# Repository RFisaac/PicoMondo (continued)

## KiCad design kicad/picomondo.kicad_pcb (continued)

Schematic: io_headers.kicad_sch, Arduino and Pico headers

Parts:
J14: Arduino power; PinSocket_1x08_P2.54mm_Vertical; MPN B-2200S08P-A120; LCSC C124416
J15: Arduino analog; PinSocket_1x06_P2.54mm_Vertical; MPN B-2200S06P-A120; LCSC C124415
J16: Arduino digital 0-7; PinSocket_1x08_P2.54mm_Vertical; MPN B-2200S08P-A120; LCSC C124416
J17: Arduino digital 8-13; PinSocket_1x10_P2.54mm_Vertical; MPN B-2200S10P-B120; LCSC C124423
J18: Pico left (pins 1-20); PinSocket_1x20_P2.54mm_Vertical; MPN B-2200S20P-A120 (1x20 female); LCSC C124410
J19: Pico right (pins 40-21); PinSocket_1x20_P2.54mm_Vertical; MPN B-2200S20P-A120 (1x20 female); LCSC C124410
JP9: AREF to 3V3; SolderJumper-2_P1.3mm_Open_RoundedPad1.0x1.5mm

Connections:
+3V3: J14.2, J14.4, J19.4, J19.5, J19.6, JP9.2 (B); also elsewhere on the board
+5V: J14.5, J14.8, J19.1, J19.2; also elsewhere on the board
/Arduino and Pico headers/AREF: J17.8, JP9.1 (A)
GND: J14.6, J14.7, J17.7, J18.3, J18.8, J18.13, J18.18, J19.3, J19.8, J19.13, J19.18; also elsewhere on the board
GPIO0: J16.2, J18.1; also elsewhere on the board
GPIO1: J16.1, J18.2; also elsewhere on the board
GPIO2: J16.3, J18.4; also elsewhere on the board
GPIO3: J16.4, J18.5; also elsewhere on the board
GPIO4: J16.5, J18.6; also elsewhere on the board
GPIO5: J16.6, J18.7; also elsewhere on the board
GPIO6: J16.7, J18.9; also elsewhere on the board
GPIO7: J16.8, J18.10; also elsewhere on the board
GPIO8: J18.11; also elsewhere on the board
GPIO9: J18.12; also elsewhere on the board
GPIO10: J18.14; also elsewhere on the board
GPIO11: J18.15; also elsewhere on the board
GPIO12: J18.16; also elsewhere on the board
GPIO13: J18.17; also elsewhere on the board
GPIO14: J18.19; also elsewhere on the board
GPIO15: J18.20; also elsewhere on the board
GPIO16: J17.5, J19.20; also elsewhere on the board
GPIO17: J17.3, J19.19; also elsewhere on the board
GPIO18: J17.6, J19.17; also elsewhere on the board
GPIO19: J17.4, J19.16; also elsewhere on the board
GPIO20: J15.5, J17.9, J19.15; also elsewhere on the board
GPIO21: J15.6, J17.10, J19.14; also elsewhere on the board
GPIO22: J19.12; also elsewhere on the board
GPIO26: J19.10; also elsewhere on the board
GPIO27: J19.9; also elsewhere on the board
GPIO28: J19.7; also elsewhere on the board
GPIO32: J17.1; also elsewhere on the board
GPIO33: J17.2; also elsewhere on the board
GPIO40: J15.1; also elsewhere on the board
GPIO41: J15.2; also elsewhere on the board
GPIO42: J15.3; also elsewhere on the board
GPIO43: J15.4; also elsewhere on the board
RUN: J14.3, J19.11; also elsewhere on the board

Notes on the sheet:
Digital 1x10: D8, D9 = GPIO32, 33; D10 SS = GPIO17; D11 MOSI = GPIO19; D12 MISO = GPIO16; D13 SCK = GPIO18; GND; AREF (joined to +3V3 only if the solder jumper is bridged); SDA, SCL.
Power header 1x8: NC, IOREF (3.3 V logic level), RESET (RUN), 3.3 V, 5 V, GND, GND, VIN (+5V).
Digital 1x8: D0 (RX) = GPIO1, D1 (TX) = GPIO0, D2-D7 = GPIO2-7.
Analog header 1x6: A0-A3 = GPIO40-43 (ADC0-3), A4 = SDA (GPIO20), A5 = SCL (GPIO21).
PICO-COMPATIBLE SOCKETS: two 1x20 female headers, 17.78 mm (700 mil) apart, in the Pico pinout. GP0 = TX, GP1 = RX (Pico convention). GP8/GP9 are also the J7/J8 output enables and GP12-15/GP22 the microSD pins: a Pico accessory must not drive them. VBUS / VSYS are the board's +5V.
ARDUINO UNO R3 SHIELD SOCKETS (female). Pin 1 of each header is at the D0 / A0 / NC / D8 end in this numbering; place them on the Uno R3 hole pattern (KiCad footprint Module:Arduino_UNO_R3 has the exact positions).

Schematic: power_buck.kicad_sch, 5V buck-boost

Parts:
C21, C22, C23, C24: 10u 50V; C_1206_3216Metric; LCSC C7432782
C25: 100n 50V; C_0402_1005Metric; MPN CL05B104KB54PNC; LCSC C307331
C26: 100u 50V; CP_Elec_8x10
C27, C28, C33: 100n 25V; C_0402_1005Metric; MPN CL05B104KB54PNC; LCSC C307331
C29, C30, C31, C32, C34, C35: 22u 16V; C_1206_3216Metric; LCSC C2985039
C36: 10u 16V; C_0805_2012Metric; MPN CL21A106KAYNNNE; LCSC C15850
C37: 10n; C_0402_1005Metric; MPN CL05B103KB5NNNC; LCSC C15195
C38: 3.3n; C_0402_1005Metric; MPN CL05B332KB5NNNC; LCSC C26404
C39: 10p; C_0402_1005Metric; not fitted
L2: 4.7u; L_Coilcraft_XAL1010-XXX; MPN XAL1010-472MED; LCSC C19271849
NT1: AGND-GND; NetTie-2_SMD_Pad0.5mm
Q1, Q2: CSD18543Q3A; VSONP-8_L3.1-W3.1-P0.65-LS3.5-BL; MPN CSD18543Q3A; LCSC C840100
R12: 10m 1% 1W; R_2512_6332Metric; MPN GX2512-2W-10mR-1%; LCSC C500718
R13: 49.9k 1%; R_0402_1005Metric; MPN 0402WGF4992TCE; LCSC C25897
R14: 33.2k 1%; R_0402_1005Metric; MPN 0402WGF3322TCE; LCSC C122548
R15: 100k; R_0402_1005Metric; MPN 0402WGF1003TCE; LCSC C25741
R16: 0; R_0402_1005Metric; MPN 0402WGF0000TCE; LCSC C17168
R17: 7.5k; R_0402_1005Metric; MPN 0402WGF7501TCE; LCSC C25918
R18: 220k 1%; R_0402_1005Metric; MPN 0402WGF2203TCE; LCSC C25767
R19: 88.7k 1%; R_0402_1005Metric; MPN 0402WGF8872TCE; LCSC C25922
R20: 10k; R_0402_1005Metric; MPN 0402WGF1002TCE; LCSC C25744
U4: TPS55288; VQFN-HR-26_L4.0-W3.5_TPS55288RPMR; MPN TPS55288RPMR; LCSC C2864583

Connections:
+3V3: R20.1; also elsewhere on the board
+5V: C34.1, C35.1, R12.2, U4.13 (ISN); also elsewhere on the board
/5V buck-boost/BOOT1: C27.1, U4.22 (BOOT1)
/5V buck-boost/BOOT2: C28.1, U4.20 (BOOT2)
/5V buck-boost/CDC: R15.1, U4.16 (CDC)
/5V buck-boost/COMP: C39.1, R17.1, U4.18 (COMP)
/5V buck-boost/DITH: C37.1, U4.7 (DITH/SYNC)
/5V buck-boost/DR1H: Q1.4 (G), U4.2 (DR1H)
/5V buck-boost/DR1L: Q2.4 (G), U4.1 (DR1L)
/5V buck-boost/EN_UVLO: R18.2, R19.1, U4.4 (EN/UVLO)
/5V buck-boost/FSW: R13.1, U4.8 (FSW)
/5V buck-boost/ILIM: R14.1, U4.17 (ILIM)
/5V buck-boost/MODE: R16.1, U4.15 (MODE)
/5V buck-boost/SW1: C27.2, L2.1, Q1.1 (S), Q1.2 (S), Q1.3 (S), Q2.5 (D), Q2.6 (D), Q2.7 (D), Q2.8 (D), Q2.9 (D), U4.23 (SW1)
/5V buck-boost/SW2: C28.2, L2.2, U4.21 (SW2), U4.25 (SW2)
/5V buck-boost/VCC_TPS: C36.1, U4.19 (VCC)
/5V buck-boost/VOUT_PRE: C29.1, C30.1, C31.1, C32.1, C33.1, R12.1, U4.11 (VOUT), U4.12 (ISP), U4.26 (VOUT)
AGND: C36.2, C37.2, C38.2, C39.2, NT1.1, R13.2, R14.2, R15.2, R16.2, R19.2, U4.10 (AGND)
GND: C21.2, C22.2, C23.2, C24.2, C25.2, C26.2, C29.2, C30.2, C31.2, C32.2, C33.2, C34.2, C35.2, NT1.2, Q2.1 (S), Q2.2 (S), Q2.3 (S), U4.9 (PGND), U4.24 (PGND); also elsewhere on the board
GPIO20: U4.6 (SDA); also elsewhere on the board
GPIO21: U4.5 (SCL); also elsewhere on the board
GPIO35: R20.2, U4.14 (FB/INT); also elsewhere on the board
unnamed: C38.1, R17.2
V_INPUT: C21.1, C22.1, C23.1, C24.1, C25.1, C26.1, Q1.5 (D), Q1.6 (D), Q1.7 (D), Q1.8 (D), Q1.9 (D), R18.1, U4.3 (VIN); also elsewhere on the board

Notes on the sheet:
OUTPUT: 4 x 22 uF 16 V ceramic on the converter side of the sense resistor (the loop is compensated for 10 uF minimum effective capacitance), plus 2 x 22 uF after it. ISP/ISN are Kelvin connections to the two ends of R_SNS: route them as a pair, separate from the power copper.
INPUT: 4 x 10 uF 50 V ceramic (about 20 uF effective after DC-bias derating, TI recommends at least 4.7 uF effective), 100 nF close to the VIN pin. Optional 100 uF bulk (DNP) for long supply leads. Place the ceramics right at the buck-side FET drain and PGND (shortest loop).
CONTROL NETWORK (all AGND returns go to the AGND island, which joins GND only at the net tie next to the VCC capacitor, as in TI's layout example).
POWER STAGE: keep V_INPUT -> Q1 -> Q2 -> GND -> input caps loop tiny; SW1/SW2 traces short and wide, top layer, no vias. Inductor: 4.7 uH, saturation current 12 A or more, DCR 12 mohm or less (Coilcraft XAL1010-472 or equivalent). 0.1 uF bootstrap caps right at BOOT/SW pins.

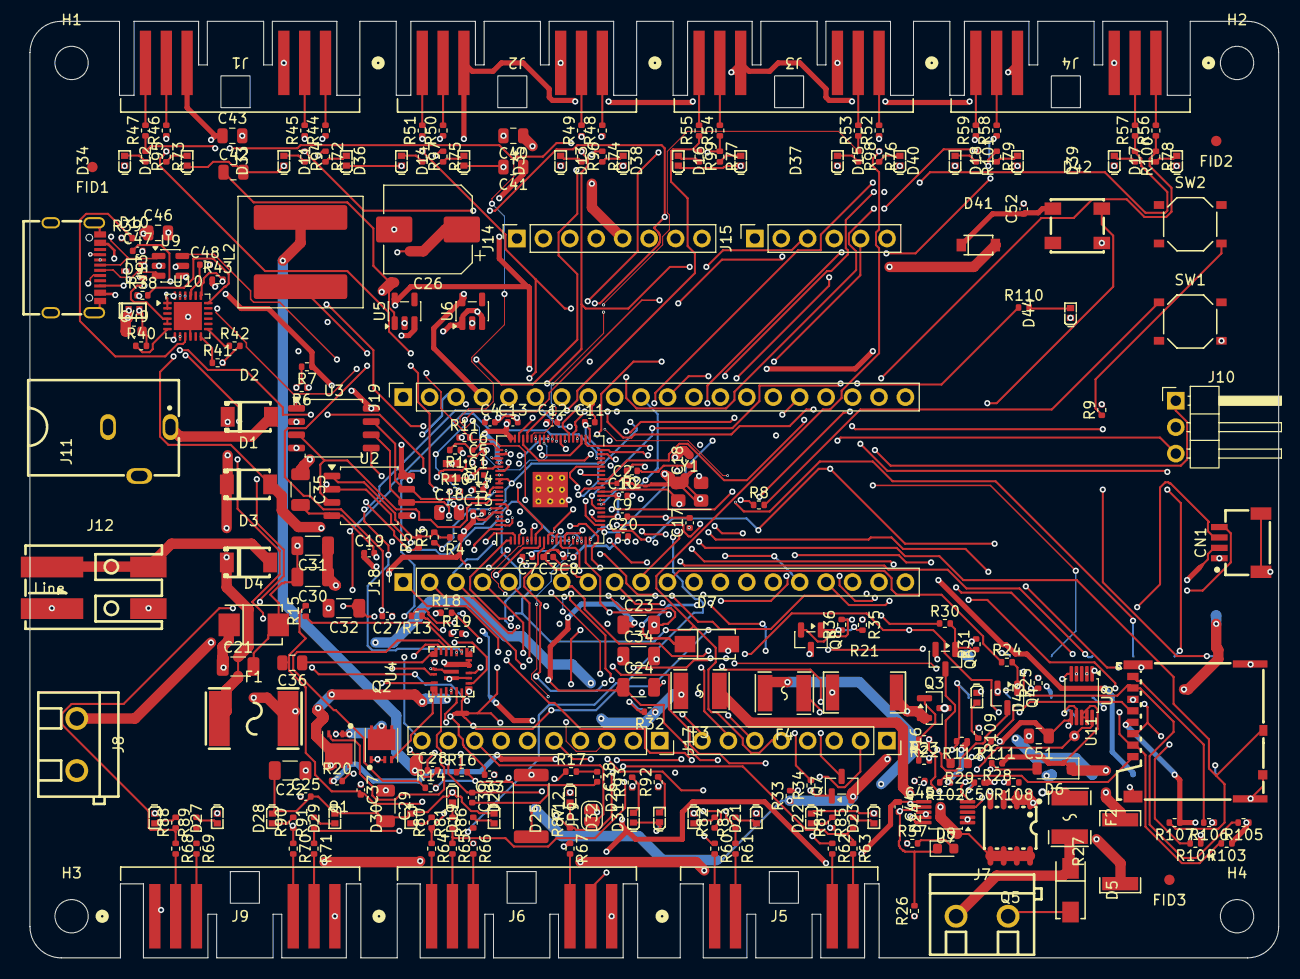
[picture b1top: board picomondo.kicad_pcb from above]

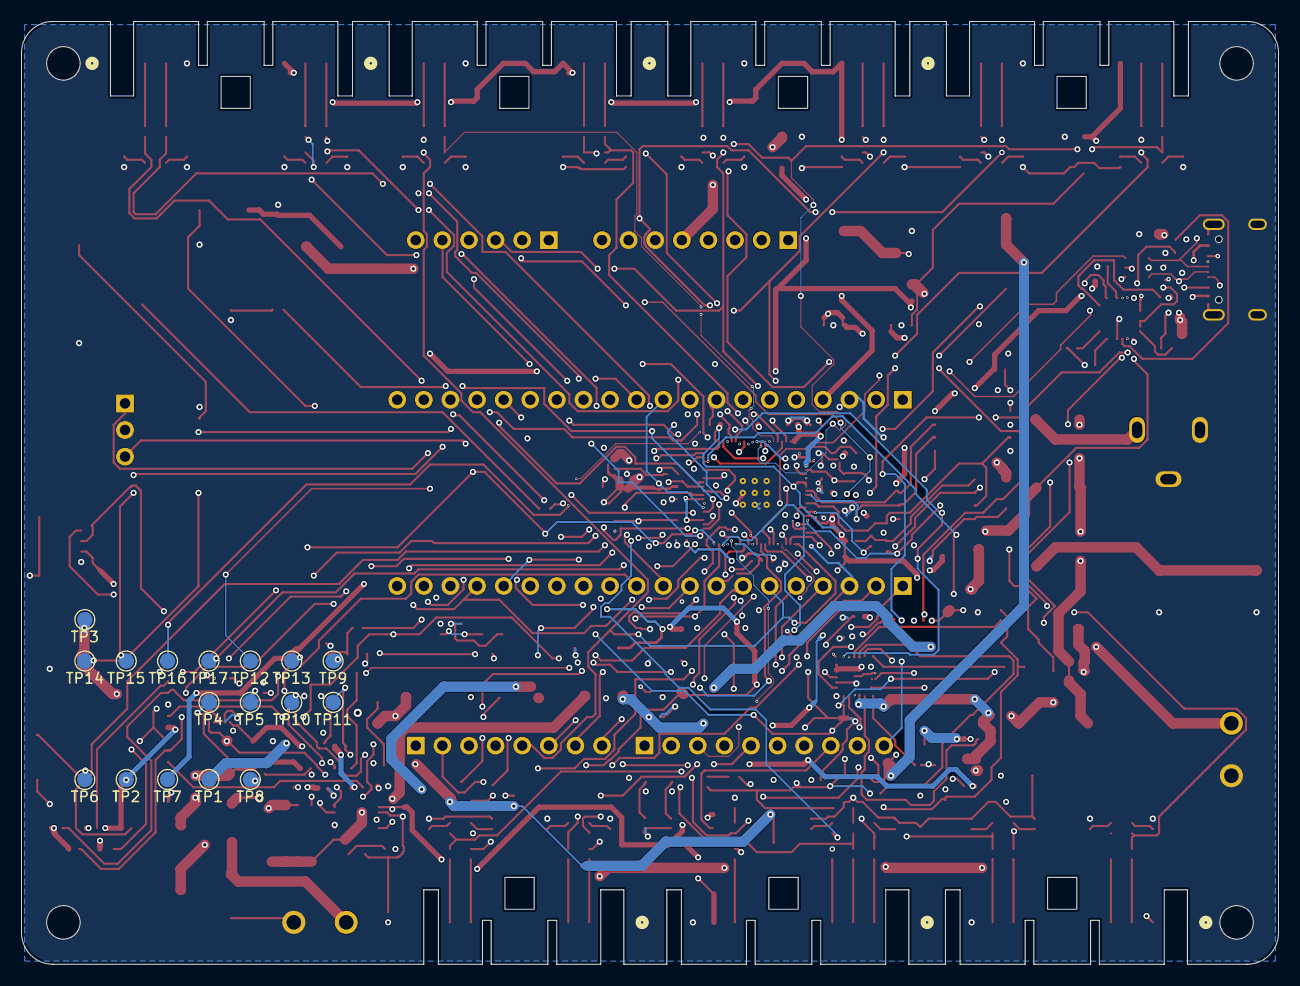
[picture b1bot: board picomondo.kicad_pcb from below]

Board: 4 copper layers, 120.0 x 90.0 mm, 282 parts (17 on the bottom side), 190 nets.

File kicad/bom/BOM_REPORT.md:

# BOM report

Generated by `tools/bom.py` from `picomondo.kicad_pcb`. 240 parts with an LCSC number on 67 line items; 46 extended or preferred line items (JLCPCB charges a loading fee per extended part type; check their current fee schedule). Stock check assumes 5 boards and a 3x margin.

## Line items

| Refs | Qty | Value | LCSC | Type | Stock | Unit price | Note |
|---|---|---|---|---|---|---|---|
| C1,C2,C5... | 4 | 4.7u | C23733 | basic | 2365245 | 0.0167 |  |
| C3,C4,C7... | 20 | 100n | C307331 | basic | 15344796 | 0.0092 |  |
| C17,C18 | 2 | 15p | C106997 | extended | 2278248 | 0.0020 |  |
| C21,C22,C23... | 4 | 10u 50V | C7432782 | extended | 100526 | 0.2051 |  |
| C29,C30,C31... | 6 | 22u 16V | C2985039 | extended | 801 | 0.3191 |  |
| C37 | 1 | 10n | C15195 | basic | 4017940 | 0.0050 |  |
| C38 | 1 | 3.3n | C26404 | preferred | 232147 | 0.0068 |  |
| C16,C36,C40... | 7 | 10u 10V | C15850 | basic | 4904066 | 0.0657 |  |
| C46 | 1 | 4.7u 25V | C1779 | basic | 2968755 | 0.0348 |  |
| C47,C48 | 2 | 1u 10V | C52923 | basic | 8321740 | 0.0108 |  |
| C49 | 1 | 1u 25V | C5673 | extended | 4396637 | 0.0278 |  |
| D1,D2,D3 | 3 | SS54F-HF 5A 40V | C5142774 | extended | 5302 | 0.2241 |  |
| D4 | 1 | SMBJ28A | C178227 | extended | 26078 | 0.1079 |  |
| D6 | 1 | BZT52C12 12V | C177013 | extended | 6524 | 0.0570 |  |
| D5,D7 | 2 | SS54-HF | C22452 | basic | 2389672 | 0.0447 |  |
| D8 | 1 | red | C2286 | basic | 4789156 | 0.0076 |  |
| D9 | 1 | ESDA25P35-1U1M | C1974707 | extended | 1426 | 0.1904 |  |
| D10 | 1 | ESDA25W | C2935152 | extended | 1027 | 0.1444 |  |
| D11,D12,D13... | 32 | white | C7220928 | extended | 545 | 0.2657 |  |
| D41 | 1 | 1N5819HW | C82544 | extended | 138574 | 0.0570 |  |
| D42 | 1 | WS2812B-V5 | C2874885 | extended | 89621 | 0.1107 |  |
| F1 | 1 | 5A hold 30V | C19078763 | extended | 68759 | 0.1610 |  |
| F2,F3,F4 | 3 | 3A hold 33V | C54300298 | extended | 5652 | 0.2187 |  |
| J7,J8 | 2 | J8 V_INPUT out | C474881 | extended | 75284 | 0.1019 |  |
| J10 | 1 | SWD | C239521 | extended | 2288 | 0.2012 |  |
| J11 | 1 | Barrel 5.5x2.1 | C3096093 | extended | 1052 | 1.0956 |  |
| J12 | 1 | Terminal 2P | C2765055 | extended | 27443 |  |  |
| J13 | 1 | USB-C | C3020560 | extended | 591 | 1.3092 |  |
| J14,J16 | 2 | Arduino power | C124416 | extended | 2667 | 0.1777 |  |
| J15 | 1 | Arduino analog | C124415 | extended | 1403 | 0.1246 |  |
| J17 | 1 | Arduino digital 8-13 | C124423 | extended | 4711 | 0.1886 |  |
| J18,J19 | 2 | Pico right (pins 40-21) | C124410 | extended | 1093 | 0.3688 |  |
| L1 | 1 | 3.3u | C42411119 | extended | 1922 | 0.2858 |  |
| L2 | 1 | 4.7u | C19271849 | extended | 157 | 13.3080 |  |
| Q1,Q2 | 2 | CSD18543Q3A | C840100 | extended | 11977 | 0.8017 |  |
| Q4,Q6,Q8 | 3 | MMBT3904 | C81464 | extended | 1556997 | 0.0167 |  |
| Q5 | 1 | DMP4015SSS-13 | C508210 | extended | 2589 | 1.2977 |  |
| Q3,Q7 | 2 | SI2305A | C347488 | extended | 47845 | 0.0409 |  |
| R1 | 1 | 33 | C25105 | basic | 1815062 | 0.0012 |  |
| R10,R11 | 2 | 27 | C25100 | extended | 56281 | 0.0019 |  |
| R12 | 1 | 10m 1% 1W | C500718 | extended | 2320 | 0.0814 |  |
| R13 | 1 | 49.9k 1% | C25897 | preferred | 35168 | 0.0015 |  |
| R14 | 1 | 33.2k 1% | C122548 | extended | 349568 | 0.0007 |  |
| R3,R16 | 2 | 0 | C17168 | basic | 9185166 | 0.0025 |  |
| R17 | 1 | 7.5k | C25918 | preferred | 1196541 | 0.0022 |  |
| R18 | 1 | 220k 1% | C25767 | preferred | 158069 | 0.0023 |  |
| R19 | 1 | 88.7k 1% | C25922 | extended | 101022 | 0.0016 |  |
| R22,R28,R33 | 3 | 47k | C25792 | basic | 5520539 | 0.0026 |  |
| R15,R25,R31... | 6 | 100k | C25741 | basic | 8203089 | 0.0025 |  |
| R21,R27 | 2 | 20m 1% 2W | C500720 | extended | 3543 | 0.0800 |  |
| R29 | 1 | 22k | C31850 | basic | 3694042 | 0.0042 |  |
| R32 | 1 | 22k | C25768 | basic | 813018 | 0.0024 |  |
| R20,R23,R24... | 14 | 10k | C25744 | basic | 21560265 | 0.0034 |  |
| R2,R8,R9... | 5 | 1k | C11702 | basic | 7068307 | 0.0019 |  |
| R43,R111,R112 | 3 | 4.7k | C25900 | basic | 15447153 | 0.0027 |  |
| R44,R45,R46... | 29 | 100 | C25076 | basic | 4079878 | 0.0013 |  |
| R37,R72,R73... | 33 | 470 | C25117 | basic | 844142 | 0.0027 |  |
| SW1,SW2 | 2 | RESET | C318884 | basic | 467503 | 0.0207 |  |
| U1 | 1 | RP2350B | C42415655 | extended | 3393 | 1.2920 |  |
| U2 | 1 | W25Q128JVS | C97521 | basic | 48814 | 2.5782 |  |
| U4 | 1 | TPS55288 | C2864583 | extended | 5147 | 2.2214 |  |
| U5,U6 | 2 | AP2112K-3.3 | C51118 | extended | 37854 | 0.1726 |  |
| U7,U8 | 2 | INA226 (0x40) | C49851 | extended | 43725 | 0.7621 |  |
| U9 | 1 | USBLC6-2SC6 | C7519 | extended | 46944 | 0.1784 |  |
| U10 | 1 | STUSB4500 | C2678061 | extended | 4876 | 2.6826 |  |
| U11 | 1 | microSD | C428492 | extended | 23940 | 1.1476 |  |
| Y1 | 1 | ABM8-272-T3 | C20625731 | extended | 12836 | 0.6255 |  |

## Through-hole parts in the BOM (not in the SMD placement file)

D1, D2, D3, D5, D7, D10, D11, D12, D13, D14, D15, D16, D17, D18, D19, D20, D21, D22, D23, D24, D25, D26, D27, D28, D29, D30, D31, D32, D33, D34, D35, D36, D37, D38, D39, D40, D43, D44, F1, F2, F3, F4, J7, J8, J11, J14, J15, J16, J17, J18, J19

## Footprint-only items (no purchase)

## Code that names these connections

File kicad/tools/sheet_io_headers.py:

"""Arduino Uno R3 shield sockets and Pico-compatible sockets.

Both header sets share the GPIO nets with the EdgeLock connectors; use one accessory class at a
time. On the PCB the Pico sockets sit inside the Arduino pin pattern so the two cannot be
plugged in together.

Arduino UART convention (resolves the old open question): D0 is RX = GPIO1, D1 is TX = GPIO0.
VIN on the Arduino power header is the board's +5V, not the raw input voltage.
"""
FP_SOCKET = "Connector_PinSocket_2.54mm:PinSocket_1x{n:02d}_P2.54mm_Vertical"
CONN = "Connector_Generic:Conn_01x{n:02d}"

ARDUINO = [
    ("Arduino power", 8, {1: None, 2: "+3V3", 3: "RUN", 4: "+3V3", 5: "+5V", 6: "GND", 7: "GND", 8: "+5V"},
     "Power header 1x8: NC, IOREF (3.3 V logic level), RESET (RUN), 3.3 V, 5 V, GND, GND, VIN (+5V)."),
    ("Arduino analog", 6, {1: "GPIO40", 2: "GPIO41", 3: "GPIO42", 4: "GPIO43", 5: "GPIO20", 6: "GPIO21"},
     "Analog header 1x6: A0-A3 = GPIO40-43 (ADC0-3), A4 = SDA (GPIO20), A5 = SCL (GPIO21)."),
    ("Arduino digital 0-7", 8, {1: "GPIO1", 2: "GPIO0", 3: "GPIO2", 4: "GPIO3", 5: "GPIO4", 6: "GPIO5",
                                7: "GPIO6", 8: "GPIO7"},
     "Digital 1x8: D0 (RX) = GPIO1, D1 (TX) = GPIO0, D2-D7 = GPIO2-7."),
    ("Arduino digital 8-13", 10, {1: "GPIO32", 2: "GPIO33", 3: "GPIO17", 4: "GPIO19", 5: "GPIO16",
                                  6: "GPIO18", 7: "GND", 8: "AREF", 9: "GPIO20", 10: "GPIO21"},
     "Digital 1x10: D8, D9 = GPIO32, 33; D10 SS = GPIO17; D11 MOSI = GPIO19; D12 MISO = GPIO16;\n"
     "D13 SCK = GPIO18; GND; AREF (joined to +3V3 only if the solder jumper is bridged); SDA, SCL."),
]

PICO_LEFT = {1: "GPIO0", 2: "GPIO1", 3: "GND", 4: "GPIO2", 5: "GPIO3", 6: "GPIO4", 7: "GPIO5", 8: "GND",
             9: "GPIO6", 10: "GPIO7", 11: "GPIO8", 12: "GPIO9", 13: "GND", 14: "GPIO10", 15: "GPIO11",
             16: "GPIO12", 17: "GPIO13", 18: "GND", 19: "GPIO14", 20: "GPIO15"}
# right row listed from Pico pin 40 down to pin 21
PICO_RIGHT = {1: "+5V", 2: "+5V", 3: "GND", 4: "+3V3", 5: "+3V3", 6: "+3V3", 7: "GPIO28", 8: "GND",
              9: "GPIO27", 10: "GPIO26", 11: "RUN", 12: "GPIO22", 13: "GND", 14: "GPIO21", 15: "GPIO20",
              16: "GPIO19", 17: "GPIO18", 18: "GND", 19: "GPIO17", 20: "GPIO16"}


def socket(s, refs, name, n, pins, x, y, mpn="", extra=None):
    c = s.add(CONN.format(n=n), refs.next("J"), name, FP_SOCKET.format(n=n), x, y,
              extra=dict(extra or {}, MPN=mpn) if mpn else extra)
    for pin, net in pins.items():
        if net is None:
            s.no_connect(c.pin(pin))
        else:
            s.attach(c.pin(pin), net, length=7.62)
    return c


def build(s, refs):
    s.note("ARDUINO UNO R3 SHIELD SOCKETS (female). Pin 1 of each header is at the D0 / A0 / NC / D8 end in this\n"
           "numbering; place them on the Uno R3 hole pattern (KiCad footprint Module:Arduino_UNO_R3 has the exact positions).",
           25.4, 25.4)
    x, y = 63.5, 76.2
    for name, n, pins, desc in ARDUINO:
        s.note(desc, x - 25.4, y - 17.78)
        c = socket(s, refs, name, n, pins, x, y, mpn="1x%d 2.54 mm female header" % n)
        if name.endswith("8-13"):
            # AREF to +3V3 through an open solder jumper (bridge to connect)
            aref = s.add("Jumper:SolderJumper_2_Open", refs.next("JP"), "AREF to 3V3",
                         "Jumper:SolderJumper-2_P1.3mm_Open_RoundedPad1.0x1.5mm", x + 55.88, y - 7.62)
            s.attach(aref.pin(1), "AREF", length=5.08)
            s.attach(aref.pin(2), "+3V3", length=5.08)
        x += 88.9
        if x > 400:
            x, y = 63.5, y + 76.2
    s.note("PICO-COMPATIBLE SOCKETS: two 1x20 female headers, 17.78 mm (700 mil) apart, in the Pico pinout.\n"
           "GP0 = TX, GP1 = RX (Pico convention). GP8/GP9 are also the J7/J8 output enables and GP12-15/GP22 the\n"
           "microSD pins: a Pico accessory must not drive them. VBUS / VSYS are the board's +5V.",
           25.4, 177.8)
    socket(s, refs, "Pico left (pins 1-20)", 20, PICO_LEFT, 63.5, 254.0, mpn="B-2200S20P-A120 (1x20 female)",
           extra={"LCSC": "C124410"})
    socket(s, refs, "Pico right (pins 40-21)", 20, PICO_RIGHT, 152.4, 254.0, mpn="B-2200S20P-A120 (1x20 female)",
           extra={"LCSC": "C124410"})

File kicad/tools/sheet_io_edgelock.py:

"""EdgeLock connectors J1-J6 and J9, and the per-GPIO indicator LEDs.

The Molex Edge Lock system (series 200890, 2.0 mm pitch) is a wire housing that clips over the
board EDGE and contacts pads on the PCB, so J1-J6 and J9 are rows of edge pads, not SMD parts.
The footprints come from Molex's own KiCad footprints, checked against Molex's sales drawing
2008900206: pads plus the board-edge cut-outs (see kicad/docs/io.md and make_edgelock_fp.py).
(Your spec's "502598-0603" is a different Molex series, a 0.3 mm flat-cable connector.)

Each signal pin has a 100 ohm series resistor between the GPIO net and the connector pad (limits
fault and ESD current from user wiring). The indicator LEDs hang on the GPIO net (shunt, about
1 mA to ground) and do not sit in the signal path.
"""
from cells import FP_R0402, res

CONN = {6: "Connector_Generic:Conn_01x06", 4: "Connector_Generic:Conn_01x04"}
FP = {6: "picomondo:EdgeLock_6ckt_Molex2008900106", 4: "picomondo:EdgeLock_4ckt_Molex2008900104"}
HOUSING = {6: "2008900106", 4: "2008900104"}

# (number, circuits, {pin: net}, description)
CONNECTORS = [
    (1, 6, {1: "GPIO0", 2: "GPIO40", 3: "GND", 4: "+3V3", 5: "GPIO1", 6: "GPIO41"},
     "J1: joystick-ready. GPIO0 and GPIO1 are also UART0 TX / RX; GPIO40/41 are ADC0 / ADC1."),
    (2, 6, {1: "GPIO2", 2: "GPIO42", 3: "GND", 4: "+3V3", 5: "GPIO3", 6: "GPIO43"},
     "J2: joystick-ready. GPIO42/43 are ADC2 / ADC3."),
    (3, 6, {1: "GPIO4", 2: "GPIO44", 3: "GND", 4: "+3V3", 5: "GPIO5", 6: "GPIO45"},
     "J3: joystick-ready. GPIO44/45 are ADC4 / ADC5."),
    (4, 6, {1: "GPIO6", 2: "GPIO46", 3: "GND", 4: "+3V3", 5: "GPIO7", 6: "GPIO47"},
     "J4: joystick-ready. GPIO46/47 are ADC6 / ADC7."),
    (5, 4, {1: "GPIO16", 2: "GPIO17", 3: "GPIO18", 4: "GPIO19"},
     "J5: SPI0 (MISO, CS, SCK, MOSI), shared with the Arduino header."),
    (6, 6, {1: "GPIO10", 2: "GPIO11", 3: "GPIO26", 4: "GPIO27", 5: "+3V3", 6: "GND"},
     "J6: UART1 (TX, RX) plus enable and IRQ lines, for serial modules."),
    (9, 6, {1: "+5V_SW", 2: "GPIO28", 3: "GPIO29", 4: "GPIO30", 5: "GPIO31", 6: "GND"},
     "J9: servo / motor connector: switched 5 V (GPIO24), four PWM-capable GPIOs."),
]

POSITIONS = {1: (88.9, 63.5), 2: (88.9, 114.3), 3: (88.9, 165.1), 4: (88.9, 215.9),
             5: (88.9, 266.7), 6: (254.0, 63.5), 9: (254.0, 114.3)}


def build(s, refs):
    s.note("Pins 1-2 and 5-6 of the 6-pin connectors carry signals; the 100 ohm series resistors protect the MCU\n"
           "from user wiring. Indicator LEDs are on the next sheet. These connectors share GPIOs with the Arduino\n"
           "and Pico headers: use one accessory class at a time.", 25.4, 25.4)
    for num, n, pins, desc in CONNECTORS:
        cx, cy = POSITIONS[num]
        c = s.add(CONN[n], refs.fixed("J", num), f"EdgeLock J{num}", FP[n], cx, cy, in_bom=False,
                  extra={"MPN": f"Molex {HOUSING[n]} (mating housing, bought separately)",
                         "NOTE": "board-edge pads and board cut-outs; no part on the board"})
        s.note(desc, cx - 38.1, cy - 17.78)
        for pin, net in pins.items():
            p = c.pin(pin)
            if net.startswith("GPIO"):
                # 100 ohm in series between the GPIO net and the connector pad
                r = s.add("Device:R", refs.next("R"), "100", FP_R0402, p.x - 5.08 - 3.81, p.y,
                          rot=90)
                s.wire(r.pin(2).pos, p.pos)
                s.attach(r.pin(1), net, length=7.62)
            else:
                s.attach(p, net, length=7.62)

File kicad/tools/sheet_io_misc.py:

"""Board support: microSD, WS2812B status LED, power and user LEDs, I2C pull-ups, test points,
mounting holes and fiducials.

microSD uses SPI mode on SPI1: GPIO12 = DAT0 (MISO), GPIO13 = CS (DAT3), GPIO14 = CLK,
GPIO15 = CMD (MOSI), GPIO22 = card detect.
"""
from cells import FP_C0402, FP_C0805, FP_R0402, cap, res

SD = "lcsc:503398-1892"
FP_SD = "lcsc:TF-SMD_503398-1892"
WS = "lcsc:WS2812B-V5_C2846931"
FP_WS = "lcsc:LED-SMD_4P-L5.0-W5.0-LS5.4-TL-1"
LED = "lcsc:LWQH8G-Q2OO-3K5L-1"
FP_LED = "lcsc:LED-SMD_L1.0-W0.5-RD_WHITE"
D_SCHOTTKY = "lcsc:1N5819HW-7-F"
FP_D = "lcsc:SOD-123_L2.7-W1.6-LS3.7-RD"

TEST_POINTS = ["+5V", "+3V3", "V_INPUT", "GND", "GND", "+1V1", "+3V3_AUX", "+5V_SW", "VBUS",
               "GPIO20", "GPIO21", "USB_D+", "USB_D-", "GPIO36", "GPIO37", "GPIO38", "GPIO39"]


def build(s, refs):
    # ------------------------------------------------------------------ microSD
    s.note("MICROSD (Molex 5033981892, push-push), SPI mode. 10 kohm pull-ups on CMD, DAT0, CS and the unused\n"
           "DAT1/DAT2 as the SD specification asks. Card detect: the two switch contacts (pins 9, 10) close when\n"
           "a card is inserted, pulling GPIO22 low. Verify pins 9/10 against Molex's drawing (not reachable here).",
           25.4, 25.4)
    u = s.add(SD, refs.next("U"), "microSD", FP_SD, 88.9, 76.2,
              extra={"MPN": "5033981892", "LCSC": "C428492"})
    for pin, net in {1: "SD_DAT2", 2: "GPIO13", 3: "GPIO15", 5: "GPIO14", 7: "GPIO12", 8: "SD_DAT1",
                     9: "GPIO22"}.items():
        s.attach(u.pin(pin), net, length=7.62)
    s.attach(u.pin(4), "+3V3", length=7.62)
    for pin in (6, 10, 11):
        s.attach(u.pin(pin), "GND", length=7.62)
    x = 152.4
    for net in ("SD_DAT2", "GPIO13", "GPIO15", "GPIO12", "SD_DAT1", "GPIO22"):
        res(s, refs, x, 63.5, "10k", "+3V3", net)
        x += 15.24
    cap(s, refs, x, 63.5, "100n", FP_C0402, "+3V3", "GND")
    cap(s, refs, x + 15.24, 63.5, "10u 10V", FP_C0805, "+3V3", "GND")

    # ------------------------------------------------------------------ WS2812B
    s.note("WS2812B-V5 STATUS LED on GPIO23. The LED needs a logic high of 0.63 x VDD (3.15 V at 5 V), which a 3.3 V GPIO\n"
           "barely reaches. A series Schottky diode drops VDD to about 4.6 V, so the threshold falls to about 2.9 V.\n"
           "100 ohm in the data line; DOUT is unused.", 25.4, 139.7)
    d = s.add(D_SCHOTTKY, refs.next("D"), "1N5819HW", FP_D, 63.5, 177.8, rot=180,
              extra={"MPN": "1N5819HW-7-F", "LCSC": "C82544"})
    s.attach(d.pin(2), "+5V", length=7.62)                # anode toward +5V
    s.attach(d.pin(1), "WS_VDD", length=7.62)
    w = s.add(WS, refs.next("D"), "WS2812B-V5", FP_WS, 139.7, 177.8,
              extra={"MPN": "WS2812B-V5", "LCSC": "C2846931"})
    s.attach(w.pin(1), "WS_VDD", length=7.62)
    s.attach(w.pin(3), "GND", length=7.62)
    s.no_connect(w.pin(2))
    r = s.add("Device:R", refs.next("R"), "100", FP_R0402, 177.8, 177.8, rot=90)
    s.attach(r.pin(1), "GPIO23", length=7.62)
    s.wire(r.pin(2).pos, w.pin(4).pos)
    cap(s, refs, 101.6, 190.5, "100n", FP_C0402, "WS_VDD", "GND")

    # ------------------------------------------------------------------ status LEDs
    s.note("STATUS LEDS: power (always on with +3V3) and user LED on GPIO25 (Pico convention). 470 ohm, about 1 mA.",
           25.4, 228.6)
    for i, (src, label) in enumerate((("+3V3", "power"), ("GPIO25", "user"))):
        x0 = 63.5 + i * 38.1
        rr = s.add("Device:R", refs.next("R"), "470", FP_R0402, x0, 254.0)
        s.attach(rr.pin(1), src, length=0 if src in ("+3V3",) else 5.08)
        led = s.add(LED, refs.next("D"), label, FP_LED, x0 + 2.54, 262.89, rot=90,
                    extra={"MPN": "LW QH8G-Q2OO-3K5L-1", "LCSC": "C7220928"}, show_value=True)
        s.wire(rr.pin(2).pos, led.pin(2).pos)
        s.attach(led.pin(1), "GND", length=0)

    # ------------------------------------------------------------------ I2C pull-ups
    s.note("I2C0 pull-ups (one set for the whole bus: STUSB4500, two INA226 and the Arduino header): 4.7 kohm to +3V3.",
           190.5, 228.6)
    res(s, refs, 203.2, 254.0, "4.7k", "+3V3", "GPIO20")
    res(s, refs, 218.44, 254.0, "4.7k", "+3V3", "GPIO21")

    # ------------------------------------------------------------------ test points
    s.note("TEST POINTS (1.5 mm pads): rails, ground, I2C, USB, and the spare GPIO36-39 for expansion.", 25.4, 292.1)
    for i, net in enumerate(TEST_POINTS):
        tp = s.add("Connector:TestPoint", refs.next("TP"), net, "TestPoint:TestPoint_Pad_D1.5mm",
                   38.1 + i * 20.32, 317.5, rot=0, show_value=True)
        s.attach(tp.pin(1), net, length=5.08)

    # ------------------------------------------------------------------ mechanical
    s.note("MECHANICAL: 4 x M3 mounting holes (Pi HAT hole spacing if practical) and 3 fiducials.", 25.4, 355.6)
    for i in range(4):
        s.add("Mechanical:MountingHole", refs.next("H"), "M3", "MountingHole:MountingHole_3.2mm_M3",
              38.1 + i * 25.4, 374.65, show_ref=True)
    for i in range(3):
        s.add("Mechanical:Fiducial", refs.next("FID"), "Fiducial", "Fiducial:Fiducial_1mm_Mask2mm",
              165.1 + i * 25.4, 374.65, show_ref=True)

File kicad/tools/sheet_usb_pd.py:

"""USB-C input with USB Power Delivery sink controller (STUSB4500).

  USB-C receptacle (USB 2.0 only) --> VBUS (to the power input sheet's diode-OR)
                                  --> D+/D- through an ESD array to the MCU (USB_D+/USB_D-)
                                  --> CC1/CC2 to the STUSB4500, which negotiates the voltage

The STUSB4500 runs in dead-battery mode (CC1DB/CC2DB tied to CC1/CC2) so a PD source always
provides VBUS. It is powered from VBUS (VDD) and from +3V3_AUX (VSYS), and configured over I2C
(address 0x28, GPIO20/GPIO21). There is no VBUS power switch: the 5 V default voltage reaches the
converter first, then the negotiated voltage. See kicad/docs/usb_pd.md.
"""
from cells import FP_C0402, FP_C0603, FP_R0402, cap, res

CONN = "lcsc:USB4105-GF-A"
PD = "Interface_USB:STUSB4500QTR"
ESD_CC = "lcsc:ESDA25W"
TVS_VBUS = "lcsc:ESDA25P35-1U1M"
ESD_USB = "Power_Protection:USBLC6-2SC6"

FP_CONN = "lcsc:TYPE-C-SMD_SBC-160S1A-20-S412"
FP_PD = "Package_DFN_QFN:QFN-24-1EP_4x4mm_P0.5mm_EP2.7x2.7mm"
FP_ESD_CC = "lcsc:SOT-323-3_L2.1-W1.3-P1.32-LS2.1-BR"
FP_TVS_VBUS = "lcsc:DFN1610-2_L1.6-W1.0-P1.05-RD"
FP_ESD_USB = "Package_TO_SOT_SMD:SOT-23-6"


def build(s, refs):
    s.note("USB-C RECEPTACLE (USB 2.0 data, power and PD). GCT USB4105-GF-A.\n"
           "Both A and B row contacts of VBUS, GND, D+ and D- are tied together so the plug can go in either way.\n"
           "SBU1/SBU2 are not used.", 25.4, 25.4)
    # ------------------------------------------------------------------ receptacle
    j = s.add(CONN, refs.next("J"), "USB-C", FP_CONN, 88.9, 114.3,
              extra={"MPN": "USB4105-GF-A", "LCSC": "C3020560"})
    for n in ("A4", "A9", "B4", "B9"):
        vbus_end = s.attach(j.pin(n), "VBUS", length=7.62)
    s.flag_net(vbus_end, direction=270)               # VBUS comes from the cable: mark it driven (ERC)
    for n in ("A1", "A12", "B1", "B12"):
        s.attach(j.pin(n), "GND", length=7.62)
    for n in ("1", "2", "3", "4"):                       # shield / mounting contacts
        s.attach(j.pin(n), "GND", length=5.08)
    s.attach(j.pin("A5"), "CC1", length=7.62)
    s.attach(j.pin("B5"), "CC2", length=7.62)
    for n in ("A6", "B6"):
        s.attach(j.pin(n), "USB_DP_CON", length=7.62)
    for n in ("A7", "B7"):
        s.attach(j.pin(n), "USB_DN_CON", length=7.62)
    s.no_connect(j.pin("A8"))
    s.no_connect(j.pin("B8"))

    # ------------------------------------------------------------------ VBUS protection and bulk
    s.note("VBUS: 4.7 uF at the connector, and a one-way 22 V TVS (ESDA25P35-1U1M, ST's reference part;\n"
           "cathode on VBUS). 20 V is the highest PD voltage requested.", 25.4, 160.02)
    cap(s, refs, 63.5, 190.5, "4.7u 25V", "Capacitor_SMD:C_0805_2012Metric", "VBUS", "GND")
    tv = s.add(TVS_VBUS, refs.next("D"), "ESDA25P35-1U1M", FP_TVS_VBUS, 88.9, 190.5, rot=270,
               extra={"MPN": "ESDA25P35-1U1M", "LCSC": "C1974707", "NOTE": "pin 1 = cathode on VBUS"})
    s.attach(tv.pin(1), "VBUS", length=5.08)
    s.attach(tv.pin(2), "GND", length=5.08)

    # ------------------------------------------------------------------ CC line ESD
    s.note("CC1 / CC2 ESD: ESDA25W dual TVS (25 V breakdown; the CC pins tolerate up to 22 V).",
           25.4, 223.52)
    esd = s.add(ESD_CC, refs.next("D"), "ESDA25W", FP_ESD_CC, 63.5, 248.92,
                extra={"MPN": "ESDA25W", "LCSC": "C2935152"})
    s.attach(esd.pin(1), "CC1", length=7.62)
    s.attach(esd.pin(2), "CC2", length=7.62)
    s.attach(esd.pin(3), "GND", length=7.62)

    # ------------------------------------------------------------------ USB 2.0 data ESD
    s.note("USB data ESD: USBLC6-2SC6. Connector side is the _CON nets; the MCU side is USB_D+/USB_D-\n"
           "(the 27 ohm series resistors are on the MCU sheet). Keep the pair 90 ohm differential.",
           165.1, 25.4)
    u2 = s.add(ESD_USB, refs.next("U"), "USBLC6-2SC6", FP_ESD_USB, 190.5, 63.5,
               extra={"MPN": "USBLC6-2SC6", "LCSC": "C7519"})
    s.attach(u2.pin(1), "USB_DP_CON", length=7.62)
    s.attach(u2.pin(6), "USB_D+", length=7.62)
    s.attach(u2.pin(3), "USB_DN_CON", length=7.62)
    s.attach(u2.pin(4), "USB_D-", length=7.62)
    s.attach(u2.pin(5), "VBUS", length=7.62)
    s.attach(u2.pin(2), "GND", length=5.08)

    # ------------------------------------------------------------------ STUSB4500
    s.note("STUSB4500 USB PD SINK CONTROLLER (I2C address 0x28). Dead-battery mode: CC1DB/CC2DB tied to CC1/CC2.\n"
           "Powered from VBUS (VDD) and +3V3_AUX (VSYS). Default contract set in its NVM (5 V 1.5 A / 15 V 1.5 A /\n"
           "20 V 1.0 A); firmware should program the wanted profile once over I2C.", 165.1, 101.6)
    u = s.add(PD, refs.next("U"), "STUSB4500", FP_PD, 254.0, 190.5,
              extra={"MPN": "STUSB4500QTR", "LCSC": "C2678061"})
    s.attach(u.pin(1), "CC1", length=7.62)       # CC1DB
    s.attach(u.pin(2), "CC1", length=7.62)       # CC1
    s.attach(u.pin(4), "CC2", length=7.62)       # CC2
    s.attach(u.pin(5), "CC2", length=7.62)       # CC2DB
    s.attach(u.pin(6), "PD_RESET", length=7.62)  # active-high reset, held low
    s.attach(u.pin(7), "GPIO21", length=7.62)    # SCL
    s.attach(u.pin(8), "GPIO20", length=7.62)    # SDA
    s.attach(u.pin(12), "PD_ADDR0", length=7.62)
    s.attach(u.pin(13), "PD_ADDR1", length=7.62)
    s.attach(u.pin(19), "GPIO34", length=7.62)   # ALERT (open drain, active low)
    s.attach(u.pin(9), "PD_DISCH", length=7.62)
    s.attach(u.pin(18), "PD_VSENSE", length=7.62)
    s.attach(u.pin(24), "VBUS", length=5.08)     # VDD
    s.attach(u.pin(22), "+3V3_AUX", length=5.08)  # VSYS
    s.attach(u.pin(23), "PD_V27", length=5.08)
    s.attach(u.pin(21), "PD_V12", length=5.08)
    s.attach(u.pin(10), "GND", length=5.08)
    s.attach(u.pin(25), "GND", length=5.08)
    for n in (3, 11, 14, 15, 16, 17, 20):        # unused (open-drain outputs and NC)
        s.no_connect(u.pin(n))

    # supporting parts
    x, y = 330.2, 114.3
    cap(s, refs, x, y, "1u 10V", FP_C0402, "PD_V27", "GND")               # VREG_2V7
    cap(s, refs, x + 15.24, y, "1u 10V", FP_C0402, "PD_V12", "GND")       # VREG_1V2
    cap(s, refs, x + 30.48, y, "1u 25V", FP_C0603, "VBUS", "GND")         # VDD decoupling
    res(s, refs, x, y + 38.1, "1k", "VBUS", "PD_VSENSE")                  # limits VBUS discharge current
    res(s, refs, x + 15.24, y + 38.1, "1k", "VBUS", "PD_DISCH")
    res(s, refs, x + 30.48, y + 38.1, "10k", "PD_RESET", "GND")
    res(s, refs, x + 45.72, y + 38.1, "100k", "PD_ADDR0", "GND")          # address 0x28
    res(s, refs, x + 60.96, y + 38.1, "100k", "PD_ADDR1", "GND")
    res(s, refs, x + 76.2, y + 38.1, "4.7k", "+3V3", "GPIO34")            # ALERT pull-up

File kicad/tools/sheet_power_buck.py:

"""5 V rail: TPS55288 buck-boost converter (V_INPUT -> +5V, up to 5 A).

Follows TI's reference circuit (TPS55288 datasheet SLVSF01B, figure 8-1) with these choices:
  * output fixed at 5 V by the chip's power-up default (internal feedback, no divider needed)
  * 400 kHz switching (RFSW 49.9k), forced-PWM at light load (MODE shorted to AGND via 0R)
  * 10 mohm output sense resistor: default current limit of 50 mV / 10 mohm = 5 A
  * both external buck-side MOSFETs are 60 V CSD18543Q3A (the 40 V low-side part in the web
    design was marginal against the 40 V absolute maximum on VIN/SW1)
  * ILIM resistor 33.2k (about 10 A average inductor limit; 330000 / R from the datasheet)
See kicad/docs/power_buck_boost.md for the design calculations.
"""
from cells import (FP_C0402, FP_C0603, FP_C0805, FP_C1206, FP_R0402, FP_R2512, cap, res)

U = "lcsc:TPS55288RPMR"
Q = "lcsc:CSD18543Q3A"
FP_TPS = "lcsc:VQFN-HR-26_L4.0-W3.5_TPS55288RPMR"
FP_Q = "lcsc:VSONP-8_L3.1-W3.1-P0.65-LS3.5-BL"
FP_L = "Inductor_SMD:L_Coilcraft_XAL1010-XXX"
FP_CP = "Capacitor_SMD:CP_Elec_8x10"


def build(s, refs):
    # ------------------------------------------------------------------ controller
    u = s.add(U, refs.next("U"), "TPS55288", FP_TPS, 299.72, 152.4,
              extra={"MPN": "TPS55288RPMR", "LCSC": "C2864583"})
    left = {1: "DR1L", 2: "DR1H", 3: "V_INPUT", 4: "EN_UVLO", 5: "GPIO21", 6: "GPIO20",
            7: "DITH", 8: "FSW", 9: "GND", 10: "AGND", 11: "VOUT_PRE", 12: "VOUT_PRE"}
    right = {13: "+5V", 14: "GPIO35", 15: "MODE", 16: "CDC", 17: "ILIM", 18: "COMP",
             19: "VCC_TPS", 20: "BOOT2", 21: "SW2", 22: "BOOT1", 23: "SW1"}
    for n, net in left.items():
        s.attach(u.pin(n), net, length=12.7)
    for n, net in right.items():
        s.attach(u.pin(n), net, length=12.7)
    s.attach(u.pin(24), "GND")
    s.attach(u.pin(25), "SW2")
    s.attach(u.pin(26), "VOUT_PRE")

    # ------------------------------------------------------------------ input capacitors
    x, y = 38.1, 63.5
    s.note("INPUT: 4 x 10 uF 50 V ceramic (about 20 uF effective after DC-bias derating, TI recommends at least\n"
           "4.7 uF effective), 100 nF close to the VIN pin. Optional 100 uF bulk (DNP) for long supply leads.\n"
           "Place the ceramics right at the buck-side FET drain and PGND (shortest loop).", x - 12.7, y - 25.4)
    for i in range(4):
        cap(s, refs, x + 12.7 * i, y, "10u 50V", FP_C1206, "V_INPUT", "GND",
            extra={"LCSC": "C7432782"})
    cap(s, refs, x + 12.7 * 4, y, "100n 50V", FP_C0402, "V_INPUT", "GND")
    bulk = s.add("Device:C_Polarized", refs.next("C"), "100u 50V", FP_CP, x + 12.7 * 5, y, dnp=True)
    s.attach(bulk.pin(1), "V_INPUT", length=5.08)
    s.attach(bulk.pin(2), "GND", length=0)

    # ------------------------------------------------------------------ buck-side FETs + inductor
    s.note("POWER STAGE: keep V_INPUT -> Q1 -> Q2 -> GND -> input caps loop tiny; SW1/SW2 traces short and wide,\n"
           "top layer, no vias. Inductor: 4.7 uH, saturation current 12 A or more, DCR 12 mohm or less\n"
           "(Coilcraft XAL1010-472 or equivalent). 0.1 uF bootstrap caps right at BOOT/SW pins.", 114.3, 160.0)
    q1 = s.add(Q, refs.next("Q"), "CSD18543Q3A", FP_Q, 152.4, 88.9,
               extra={"MPN": "CSD18543Q3A", "LCSC": "C840100"})
    s.bus([q1.pin(1), q1.pin(2), q1.pin(3)], "SW1")            # source -> switch node
    s.attach(q1.pin(4), "DR1H", length=7.62)
    s.bus([q1.pin(n) for n in (5, 6, 7, 8, 9)], "V_INPUT")      # drain -> input
    q2 = s.add(Q, refs.next("Q"), "CSD18543Q3A", FP_Q, 152.4, 127.0,
               extra={"MPN": "CSD18543Q3A", "LCSC": "C840100"})
    s.bus([q2.pin(1), q2.pin(2), q2.pin(3)], "GND")            # source -> ground
    s.attach(q2.pin(4), "DR1L", length=7.62)
    s.bus([q2.pin(n) for n in (5, 6, 7, 8, 9)], "SW1")          # drain -> switch node

    l1 = s.add("Device:L", refs.next("L"), "4.7u", FP_L, 215.9, 109.22, rot=90,
               extra={"MPN": "XAL1010-472MED", "LCSC": "C19271849",
                      "NOTE": "4.7uH, Isat 25A, DCR 10 mohm (TI reference inductor)"})
    s.attach(l1.pin(1), "SW1", length=5.08)
    s.attach(l1.pin(2), "SW2", length=5.08)
    cap(s, refs, 190.5, 63.5, "100n 25V", FP_C0402, "BOOT1", "SW1")
    cap(s, refs, 215.9, 63.5, "100n 25V", FP_C0402, "BOOT2", "SW2")

    # ------------------------------------------------------------------ output and current sense
    x, y = 400.05, 63.5
    s.note("OUTPUT: 4 x 22 uF 16 V ceramic on the converter side of the sense resistor (the loop is compensated\n"
           "for 10 uF minimum effective capacitance), plus 2 x 22 uF after it. ISP/ISN are Kelvin\n"
           "connections to the two ends of R_SNS: route them as a pair, separate from the power copper.",
           x - 25.4, y - 25.4)
    for i in range(4):
        cap(s, refs, x + 12.7 * i, y + 38.1, "22u 16V", FP_C1206, "VOUT_PRE", "GND",
            extra={"LCSC": "C2985039"})
    cap(s, refs, x + 12.7 * 4, y + 38.1, "100n 25V", FP_C0402, "VOUT_PRE", "GND")
    sns = s.add("Device:R", refs.next("R"), "10m 1% 1W", FP_R2512, x - 12.7, y + 12.7, rot=90,
                extra={"MPN": "GX2512-2W-10mR-1%", "LCSC": "C500718"})
    s.attach(sns.pin(1), "VOUT_PRE", length=7.62)
    s.attach(sns.pin(2), "+5V", length=7.62)
    for i in range(2):
        cap(s, refs, x + 12.7 * i, y + 83.82, "22u 16V", FP_C1206, "+5V", "GND",
            extra={"LCSC": "C2985039"})
    s.flag("+5V", (x + 12.7 * 3, y + 76.2))

    # ------------------------------------------------------------------ control network
    x, y = 63.5, 215.9
    s.note("CONTROL NETWORK (all AGND returns go to the AGND island, which joins GND only at the net tie\n"
           "next to the VCC capacitor, as in TI's layout example).", x - 12.7, y - 25.4)
    cap(s, refs, x, y, "10u 16V", FP_C0805, "VCC_TPS", "AGND")                      # VCC bypass
    s.flag("AGND", (x - 12.7, y + 12.7))
    res(s, refs, x + 25.4, y, "49.9k 1%", "FSW", "AGND")                              # 400 kHz
    cap(s, refs, x + 50.8, y, "10n", FP_C0402, "DITH", "AGND")                        # spread spectrum
    res(s, refs, x + 76.2, y, "33.2k 1%", "ILIM", "AGND")                             # ~10 A avg limit
    res(s, refs, x + 101.6, y, "100k", "CDC", "AGND")                                 # cable comp unused
    res(s, refs, x + 127.0, y, "0", "MODE", "AGND",
        extra={"NOTE": "0R = internal VCC, I2C 0x74, forced PWM. 6.19k = PFM at light load"})
    # loop compensation: COMP -> R_c + C_c to AGND, optional C_p in parallel
    rc = s.add("Device:R", refs.next("R"), "7.5k", FP_R0402, x + 152.4, y)
    cc = s.add("Device:C", refs.next("C"), "3.3n", FP_C0402, x + 152.4, y + 7.62)
    s.attach(rc.pin(1), "COMP", length=5.08)
    s.attach(cc.pin(2), "AGND", length=0)
    cap(s, refs, x + 165.1, y, "10p", FP_C0402, "COMP", "AGND", dnp=True)
    # EN/UVLO divider on V_INPUT: turn-on about 4.3 V, turn-off about 3.2 V
    ra = s.add("Device:R", refs.next("R"), "220k 1%", FP_R0402, x + 190.5, y)
    rb = s.add("Device:R", refs.next("R"), "88.7k 1%", FP_R0402, x + 190.5, y + 7.62)
    s.attach(ra.pin(1), "V_INPUT", length=5.08)
    s.attach(rb.pin(2), "AGND", length=0)
    node = ra.pin(2).pos
    end = (node[0] + 10.16, node[1])
    s.wire(node, end)
    s.label("EN_UVLO", end, 0)
    # fault output pull-up (FB/INT is a fault indicator with internal feedback)
    res(s, refs, x + 215.9, y, "10k", "+3V3", "GPIO35")
    # AGND <-> GND tie
    nt = s.add("Device:NetTie_2", refs.next("NT"), "AGND-GND", "NetTie:NetTie-2_SMD_Pad0.5mm",
               x + 241.3, y + 5.08, show_value=False)
    s.attach(nt.pin(1), "AGND", length=5.08)
    s.attach(nt.pin(2), "GND", length=5.08)
